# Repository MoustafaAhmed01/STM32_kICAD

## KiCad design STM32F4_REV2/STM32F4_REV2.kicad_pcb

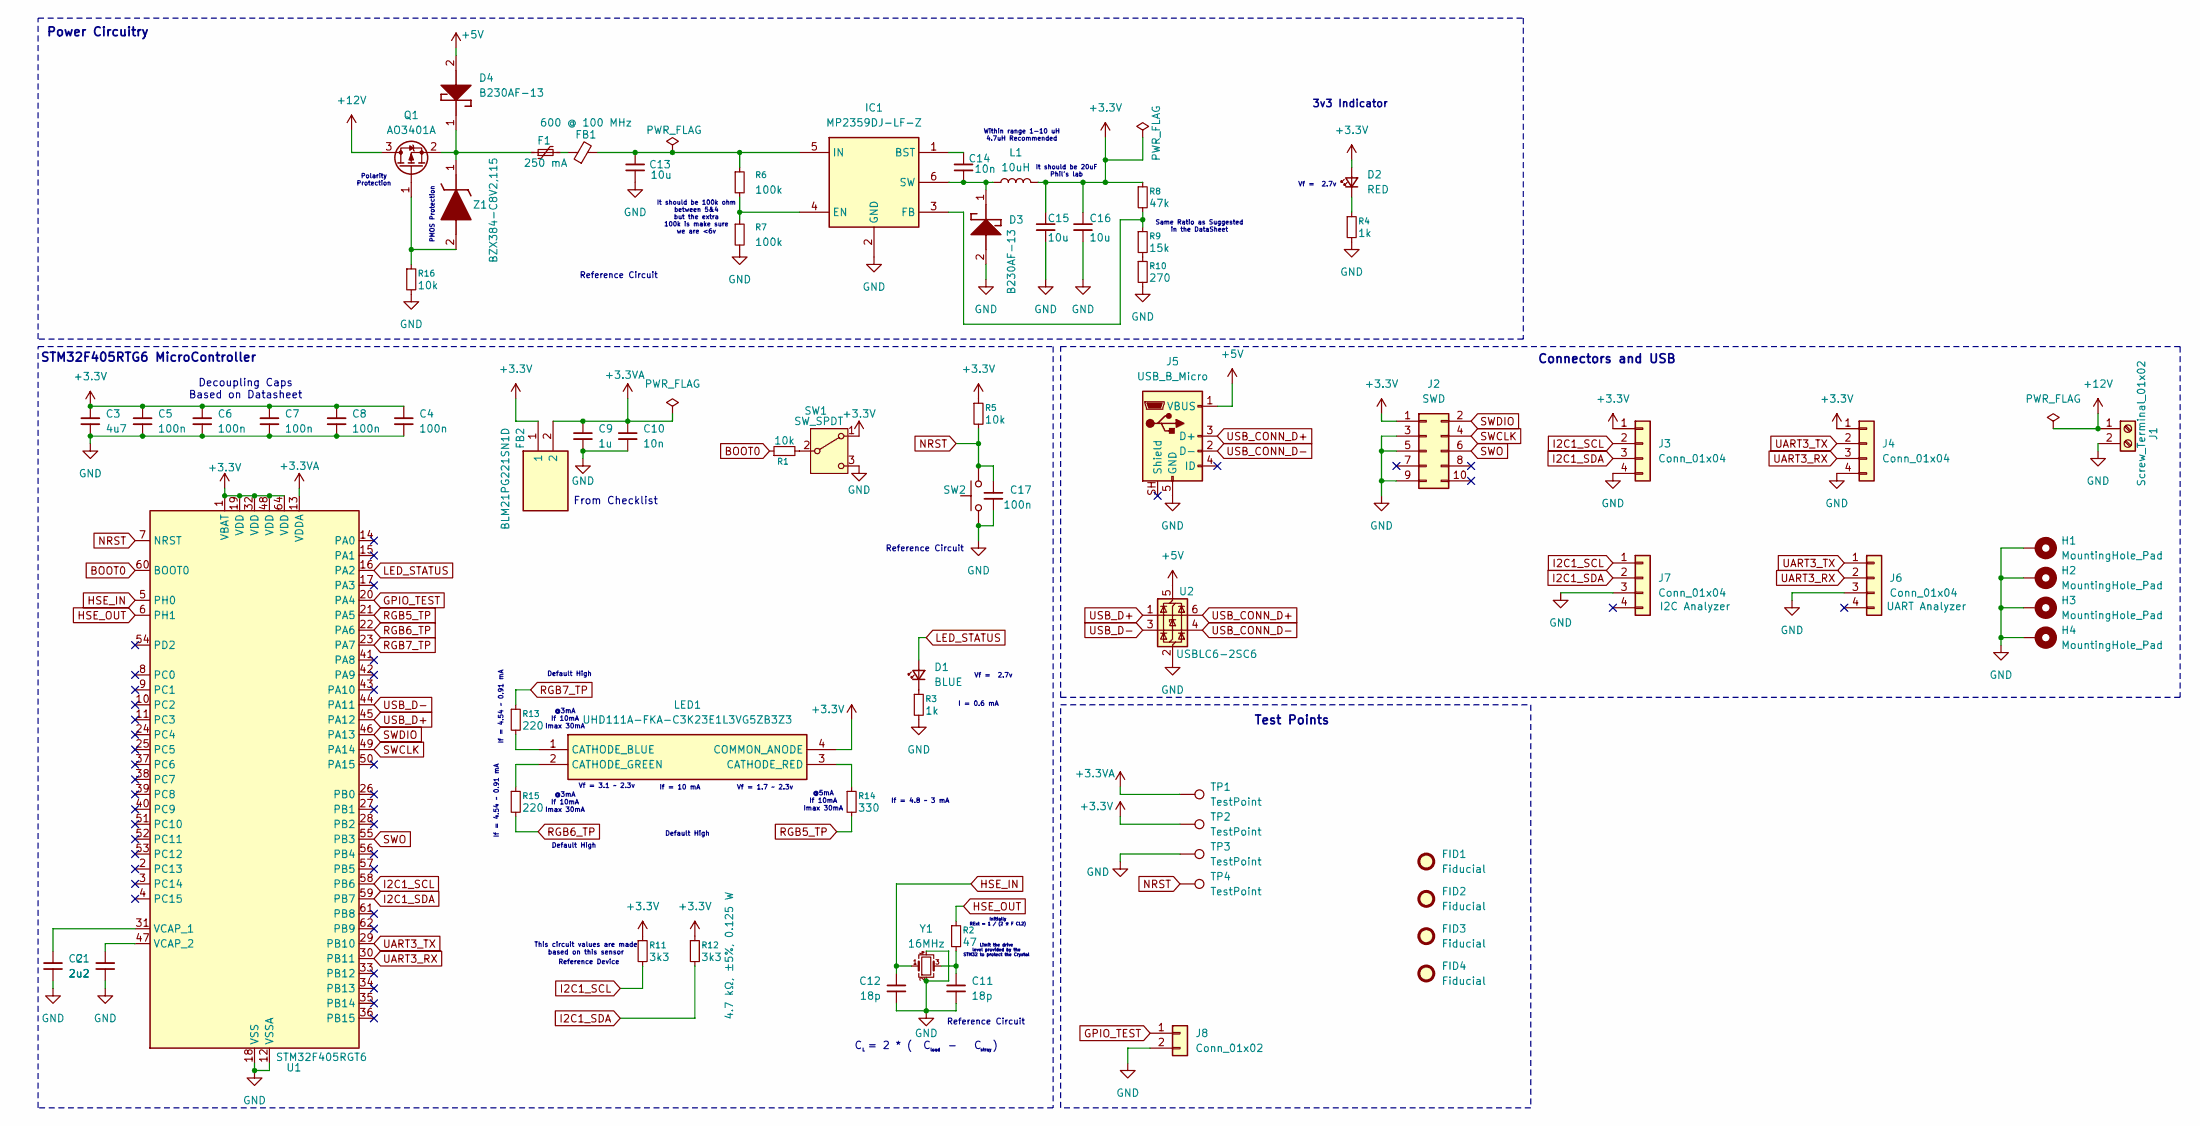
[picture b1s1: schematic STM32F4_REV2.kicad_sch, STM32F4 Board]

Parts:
C1, C2: 2u2; C_0805_2012Metric
C3: 4u7; C_0805_2012Metric
C4, C5, C6, C7, C8, C17: 100n; C_0805_2012Metric
C9: 1u; C_0805_2012Metric
C10, C14: 10n; C_0805_2012Metric
C11, C12: 18p; C_0805_2012Metric
C13, C15, C16: 10u; C_1206_3216Metric
D1: BLUE; LED_0805_2012Metric
D2: RED; LED_0805_2012Metric
D3, D4: B230AF-13; SODFL5226X110N; Mouser Part Number 621-B230AF-13
F1: 250 mA; Fuse_1206_3216Metric
FB1: 600 @ 100 MHz; C_0805_2012Metric
FB2: BLM21PG221SN1D; BEADC2012X105N; Mouser Part Number 81-BLM21P221SG
FID1, FID2, FID3, FID4: Fiducial; Fiducial_1mm_Mask2mm
H1, H2, H3, H4: MountingHole_Pad; MountingHole_4.3mm_M4_Pad_Via
IC1: MP2359DJ-LF-Z; Mouser Part Number 946-MP2359DJLFZ
J1: Screw_Terminal_01x02; TerminalBlock_Phoenix_PT-1,5-2-3.5-H_1x02_P3.50mm_Horizontal
J2: SWD; PinHeader_2x05_P1.27mm_Vertical_SMD
J3, J4: Conn_01x04; Molex_PicoBlade_53048-0410_1x04_P1.25mm_Horizontal
J5: USB_B_Micro; 101181930001LF
J6, J7: Conn_01x04; PinHeader_1x04_P2.54mm_Vertical
J8: Conn_01x02; PinHeader_1x02_P2.54mm_Vertical
L1: 10uH; L_Sunlord_MWSA0518S
LED1: UHD111A-FKA-C3K23E1L3VG5ZB3Z3; UHD111AFKAC3K23E1L3VG5ZB3Z3; Mouser Part Number 941-UHD1AA3K3E3V53Z3
Q1: AO3401A; SOT-23
R1, R5, R16: 10k; R_0805_2012Metric
R2: 47; R_0805_2012Metric
R3, R4: 1k; R_0805_2012Metric
R6, R7: 100k; R_0805_2012Metric
R8: 47k; R_0805_2012Metric
R9: 15k; R_0805_2012Metric
R10: 270; R_0805_2012Metric
R11, R12: 3k3; R_0805_2012Metric
R13, R15: 220; R_0805_2012Metric
R14: 330; R_0805_2012Metric
SW1: SW_SPDT; SW_SPDT_PCM12
SW2: SW_Push; SW_PUSH_6mm_H5mm
TP1, TP2, TP3, TP4: TestPoint; TestPoint_Pad_D1.5mm
U1: STM32F405RGT6; LQFP-64_10x10mm_P0.5mm
U2: USBLC6-2SC6; SOT-23-6
Y1: 16MHz; Crystal_SMD_3225-4Pin_3.2x2.5mm
Z1: BZX384-C8V2,115; SOD2512X110N; Mouser Part Number 771-BZX384-C8V2115

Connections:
+3.3V: C3.1, C4.1, C5.1, C6.1, C7.1, C8.1, C15.1, C16.1, D2.2 (A), FB2.1, J2.1, J3.1, J4.1, L1.2, LED1.4 (COMMON_ANODE), R5.1, R8.1, R11.1, R12.1, SW1.1 (A), TP2.1 (1_1), U1.1 (VBAT), U1.19 (VDD), U1.32 (VDD), U1.48 (VDD), U1.64 (VDD)
+3.3VA: C9.1, C10.1, FB2.2, TP1.1 (1_1), U1.13 (VDDA)
+5V: D4.2 (A), J5.1 (VBUS), U2.5 (VBUS)
+12V: J1.1, Q1.3 (D)
BOOT0: R1.1, U1.60 (BOOT0)
GND: C1.2, C2.2, C3.2, C4.2, C5.2, C6.2, C7.2, C8.2, C9.2, C10.2, C11.2, C12.2, C13.2, C15.2, C16.2, C17.2, D3.2 (A), H1.1 (1_1), H2.1 (1_1), H3.1 (1_1), H4.1 (1_1), IC1.2 (GND), J1.2, J2.3, J2.5, J2.9, J3.4, J4.4, J5.5 (GND), J6.3, J7.3, J8.2, R3.2, R4.2, R7.2, R10.2, R16.2, SW1.3 (C), SW2.1, TP3.1 (1_1), U1.12 (VSSA), U1.18 (VSS), U1.63 (VSS), U2.2 (GND), Y1.2 (G), Y1.4 (G)
GPIO_TEST: J8.1, U1.20 (PA4)
HSE_IN: C12.1, U1.5 (PH0), Y1.1
HSE_OUT: R2.1, U1.6 (PH1)
I2C1_SCL: J3.2, J7.1, R11.2, U1.58 (PB6)
I2C1_SDA: J3.3, J7.2, R12.2, U1.59 (PB7)
LED_STATUS: D1.2 (A), U1.16 (PA2)
NRST: C17.1, R5.2, SW2.2, TP4.1 (1_1), U1.7 (NRST)
unnamed: C11.1, R2.2, Y1.3
unnamed: D1.1 (K), R3.1
unnamed: D2.1 (K), R4.1
unnamed: C14.1, D3.1 (K), IC1.6 (SW), L1.1
unnamed: D4.1 (K), F1.1, Q1.2 (S), Z1.1 (K)
unnamed: F1.2, FB1.1
unnamed: C14.2, IC1.1 (BST)
unnamed: IC1.4 (EN), R6.2, R7.1
unnamed: IC1.3 (FB), R8.2, R9.1
unnamed: C13.1, FB1.2, IC1.5 (IN), R6.1
unnamed: LED1.1 (CATHODE_BLUE), R13.2
unnamed: LED1.2 (CATHODE_GREEN), R15.1
unnamed: LED1.3 (CATHODE_RED), R14.1
unnamed: Q1.1 (G), R16.1, Z1.2 (A)
unnamed: R9.2, R10.1
unnamed: R1.2, SW1.2 (B)
unnamed: C2.1, U1.31 (VCAP_1)
unnamed: C1.1, U1.47 (VCAP_2)
RGB5_TP: R14.2, U1.21 (PA5)
RGB6_TP: R15.2, U1.22 (PA6)
RGB7_TP: R13.1, U1.23 (PA7)
SWCLK: J2.4, U1.49 (PA14)
SWDIO: J2.2, U1.46 (PA13)
SWO: J2.6, U1.55 (PB3)
UART3_RX: J4.3, J6.2, U1.30 (PB11)
UART3_TX: J4.2, J6.1, U1.29 (PB10)
USB_CONN_D+: J5.3 (D+), U2.6 (I/O1)
USB_CONN_D-: J5.2 (D-), U2.4 (I/O2)
USB_D+: U1.45 (PA12), U2.1 (I/O1)
USB_D-: U1.44 (PA11), U2.3 (I/O2)

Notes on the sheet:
@3mA If 10mA Imax 30mA
Default High
Within range 1-10 uH 4.7uH Recommended
Limit the drive level provided by the STM32 to protect the Crystal
Initially RExt = 1 / (2 π F CL2)
If = 10 mA
Power Circuitry
Test Points
Vf = 3.1 ~ 2.3v
Reference Circuit
From Checklist
It should be 20uF Phil's lab
Same Ratio as Suggested in the DataSheet
It should be 100k ohm between 5&4 but the extra 100k is make sure we are <6v
Connectors and USB
If = 4.54 ~ 0.91 mA
Polarity Protection
stray
Vf = 2.7v
3v3 Indicator
This circuit values are made based on this sensor
@5mA If 10mA Imax 30mA
Vf = 1.7 ~ 2.3v
load
Decoupling Caps Based on Datasheet
I = 0.6 mA
PMOS Protection
STM32F405RTG6 MicroController
C = 2 * ( C - C )
If = 4.8 ~ 3 mA
Reference Device

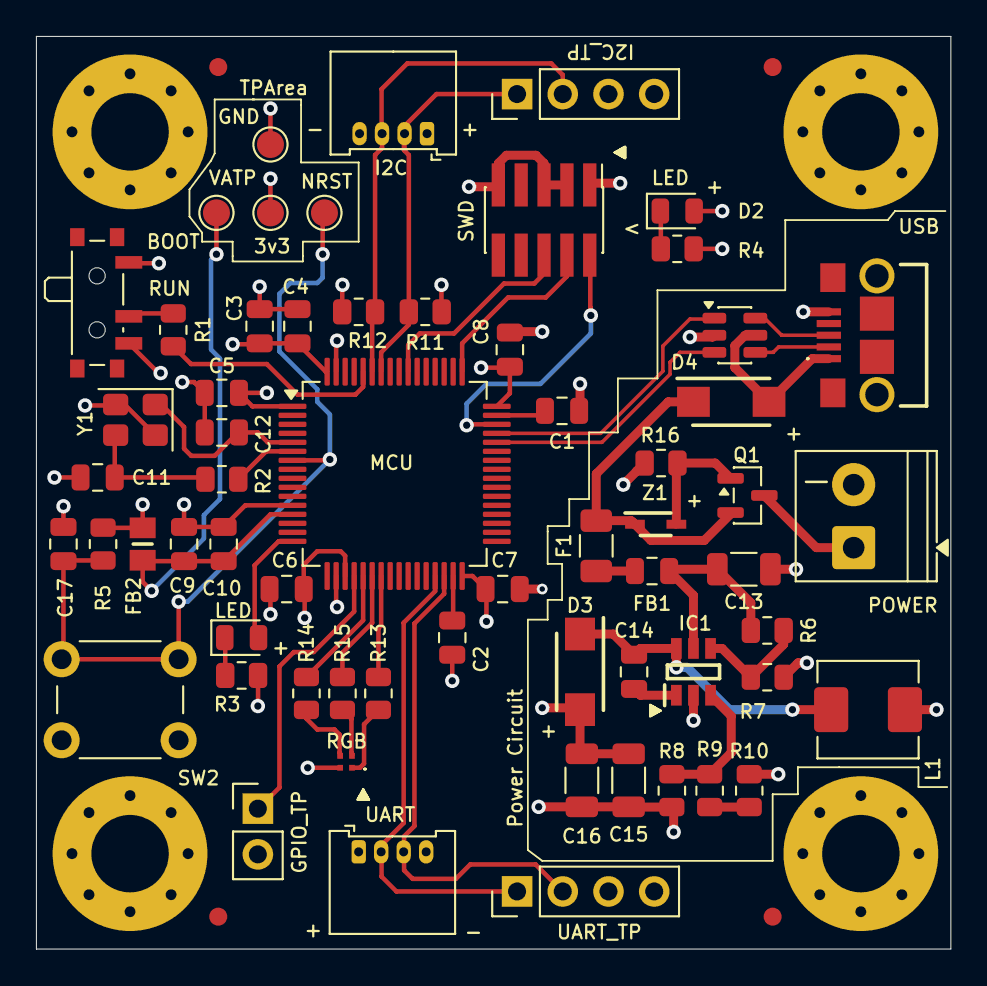
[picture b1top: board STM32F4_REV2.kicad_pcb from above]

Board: 4 copper layers, 50.8 x 50.7 mm, 70 parts (0 on the bottom side), 43 nets.
